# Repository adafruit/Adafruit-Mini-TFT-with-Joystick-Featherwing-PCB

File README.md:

## Adafruit Mini Color TFT with Joystick FeatherWing PCB

<a href="http://www.adafruit.com/products/3321"><br/>
Click here to purchase one from the Adafruit shop</a>

PCB files for the Adafruit Mini Color TFT with Joystick FeatherWing. Format is EagleCAD schematic and board layout
* https://www.adafruit.com/product/3321

### Description

Add a dazzling color display to your Feather project with this **Adafruit Mini Color TFT with Joystick FeatherWing**.

It has so much stuff going on, we could not fit any more parts on the PCB! There's a **0.96" 160x80 Color TFT Display** with 16-bit full color capability. And, so you can make a proper UI we added a 5-way navigation switch and two push buttons. The joystick can go left, right, up, down and 'in' for selection. Two buttons on the side can change modes or whatever you like.

Thanks to **seesaw** the 7 user interface switches are managed over I2C so you don't need any extra GPIO pins to spare, this display will even work on low-pin-availability Feathers like the ESP8266. All you need is the standard hardware SPI, I2C and two GPIO for TFT control. Heck, even the TFT reset pin and backlight is controlled by seesaw, all over I2C!

This lovely little display breakout is a great way to add a small, colorful and bright display to any Feather project, and it works with all of our Feathers. Since the display uses 4-wire SPI to communicate and has its own pixel-addressable frame buffer, it can be used with every kind of microcontroller. Even a very small one with low memory and few pins available.

Tested working with **all Feather boards**. [Check out our range of Feather boards here](https://www.adafruit.com/feather).

### License

Adafruit invests time and resources providing this open source design, please support Adafruit and open-source hardware by purchasing products from [Adafruit](https://www.adafruit.com)!

Designed by Limor Fried/Ladyada for Adafruit Industries.

Creative Commons Attribution/Share-Alike, all text above must be included in any redistribution. See license.txt for additional details.

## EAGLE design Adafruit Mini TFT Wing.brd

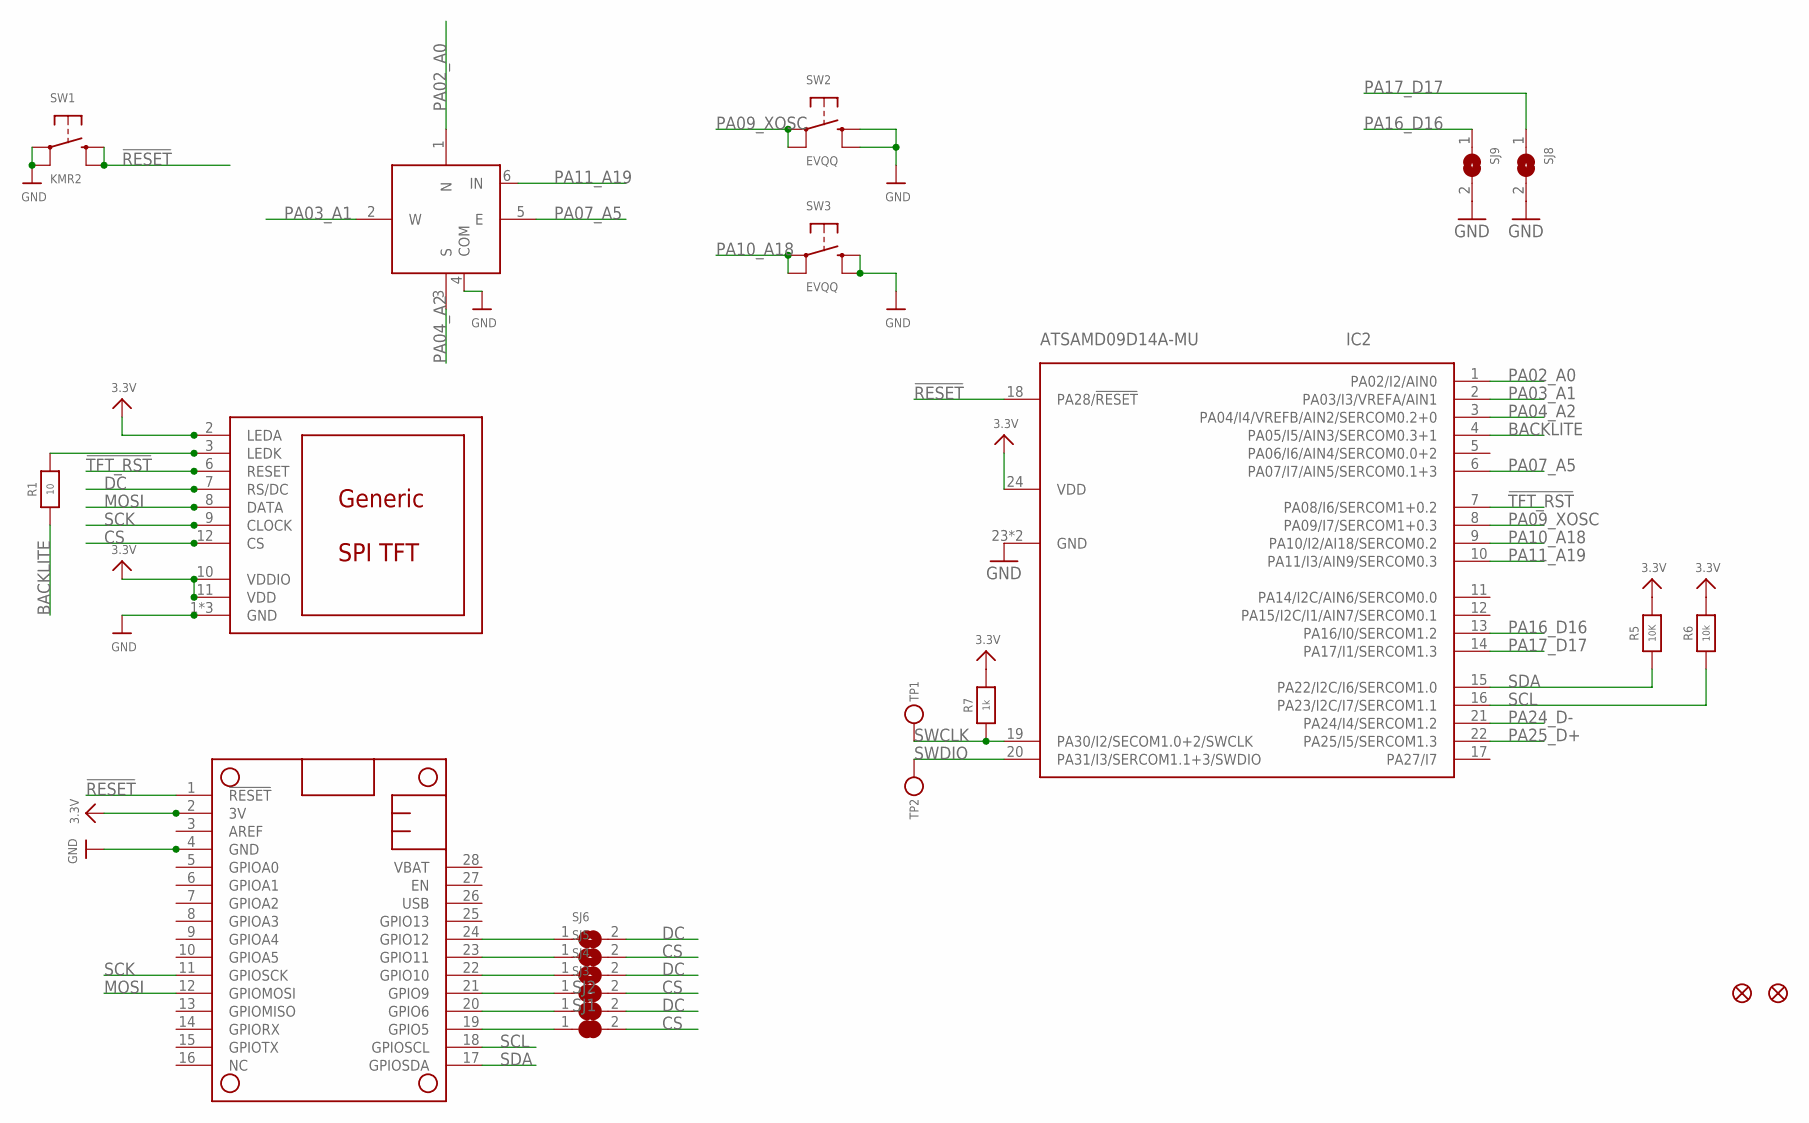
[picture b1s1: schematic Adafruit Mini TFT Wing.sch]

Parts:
FID1, FID2: FIDUCIAL_1MM
IC2: ATSAMD09D14A-MU; QFN24_4MM
MS1: FEATHERWING
R1: 10; 0603-NO
R5: 10K; 0603-NO
R6: 10k; 0603-NO
R7: 1k; 0603-NO
SJ1, SJ2: SOLDERJUMPER_CLOSED; SOLDERJUMPER_CLOSEDWIRE
SJ3, SJ4, SJ5, SJ6, SJ8, SJ9: SOLDERJUMPER; SOLDERJUMPER_ARROW_NOPASTE
SW1: KMR2; BTN_KMR2_4.6X2.8
SW2, SW3: EVQQ; EVQ-Q2_SMALLER
SW4: NAVSWITCHSKQUABAUE010; SKQUBAE010
TP1, TP2: TESTPOINTROUND2MM; TESTPOINT_ROUND_2MM
U$2: DISP_LCD_0.9IN_160X80; TFT_0.96IN_160X80

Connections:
3.3V: IC2.24 (VDD), MS1.2 (3V), R5.2, R6.2, R7.2, U$2.2 (LEDA), U$2.10 (VDDIO), U$2.11 (VDD)
!RESET: IC2.18 (PA28/!RESET), MS1.1 (!RESET), SW1.B (S), SW1.B' (S1)
!TFT_RST: IC2.7 (PA08/I6/SERCOM1+0.2), U$2.6 (RESET)
BACKLITE: IC2.4 (PA05/I5/AIN3/SERCOM0.3+1), R1.1
CS: SJ1.2, SJ3.2, SJ5.2, U$2.12 (CS)
DC: SJ2.2, SJ4.2, SJ6.2, U$2.7 (RS/DC)
GND: IC2.23 (GND), IC2.THERM (GND), MS1.4 (GND), SJ8.2, SJ9.2, SW1.A, SW1.A' (P1), SW2.B (S), SW2.B' (S1), SW3.B (S), SW3.B' (S1), SW4.4 (COM), U$2.1 (GND), U$2.5 (GND), U$2.13 (GND)
MOSI: MS1.12 (GPIOMOSI), U$2.8 (DATA)
unnamed: MS1.20 (GPIO6), SJ2.1
unnamed: MS1.19 (GPIO5), SJ1.1
unnamed: MS1.21 (GPIO9), SJ3.1
unnamed: MS1.22 (GPIO10), SJ4.1
unnamed: MS1.23 (GPIO11), SJ5.1
unnamed: MS1.24 (GPIO12), SJ6.1
unnamed: R1.2, U$2.3 (LEDK)
PA02_A0: IC2.1 (PA02/I2/AIN0), SW4.1 (N)
PA03_A1: IC2.2 (PA03/I3/VREFA/AIN1), SW4.2 (W)
PA04_A2: IC2.3 (PA04/I4/VREFB/AIN2/SERCOM0.2+0), SW4.3 (S)
PA07_A5: IC2.6 (PA07/I7/AIN5/SERCOM0.1+3), SW4.5 (E)
PA09_XOSC: IC2.8 (PA09/I7/SERCOM1+0.3), SW2.A, SW2.A' (P1)
PA10_A18: IC2.9 (PA10/I2/AI18/SERCOM0.2), SW3.A, SW3.A' (P1)
PA11_A19: IC2.10 (PA11/I3/AIN9/SERCOM0.3), SW4.6 (IN)
PA16_D16: IC2.13 (PA16/I0/SERCOM1.2), SJ9.1
PA17_D17: IC2.14 (PA17/I1/SERCOM1.3), SJ8.1
PA24_D-: IC2.21 (PA24/I4/SERCOM1.2)
PA25_D+: IC2.22 (PA25/I5/SERCOM1.3)
SCK: MS1.11 (GPIOSCK), U$2.9 (CLOCK)
SCL: IC2.16 (PA23/I2C/I7/SERCOM1.1), MS1.18 (GPIOSCL), R6.1
SDA: IC2.15 (PA22/I2C/I6/SERCOM1.0), MS1.17 (GPIOSDA), R5.1
SWCLK: IC2.19 (PA30/I2/SECOM1.0+2/SWCLK), R7.1, TP1.P$1
SWDIO: IC2.20 (PA31/I3/SERCOM1.1+3/SWDIO), TP2.P$1

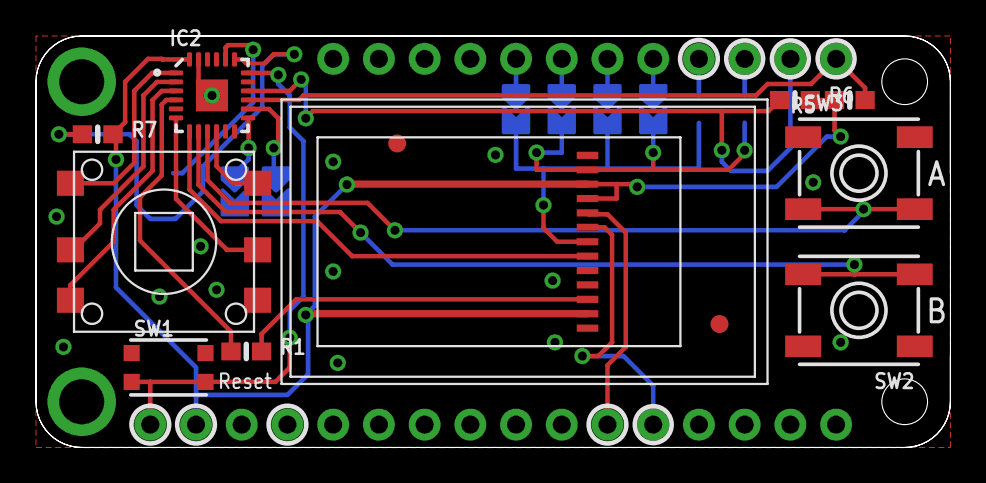
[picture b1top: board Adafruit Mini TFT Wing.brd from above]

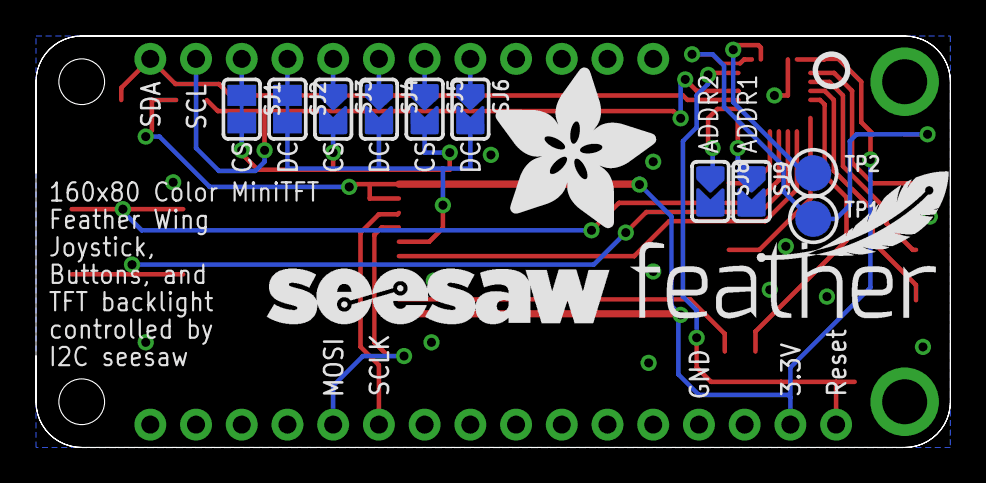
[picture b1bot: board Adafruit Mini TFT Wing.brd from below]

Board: 2 copper layers, 50.8 x 22.9 mm, 27 parts (14 on the bottom side), 29 nets.

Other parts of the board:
U$4: FEATHERLOGO_MED
U$8: SEESAW_LOGO
U$12: ADAFRUIT_9MM
U$14: PCBFEAT-REV-040

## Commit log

2018-11-03 init
2019-07-16 updated to use cookiecutter for pcb repos
